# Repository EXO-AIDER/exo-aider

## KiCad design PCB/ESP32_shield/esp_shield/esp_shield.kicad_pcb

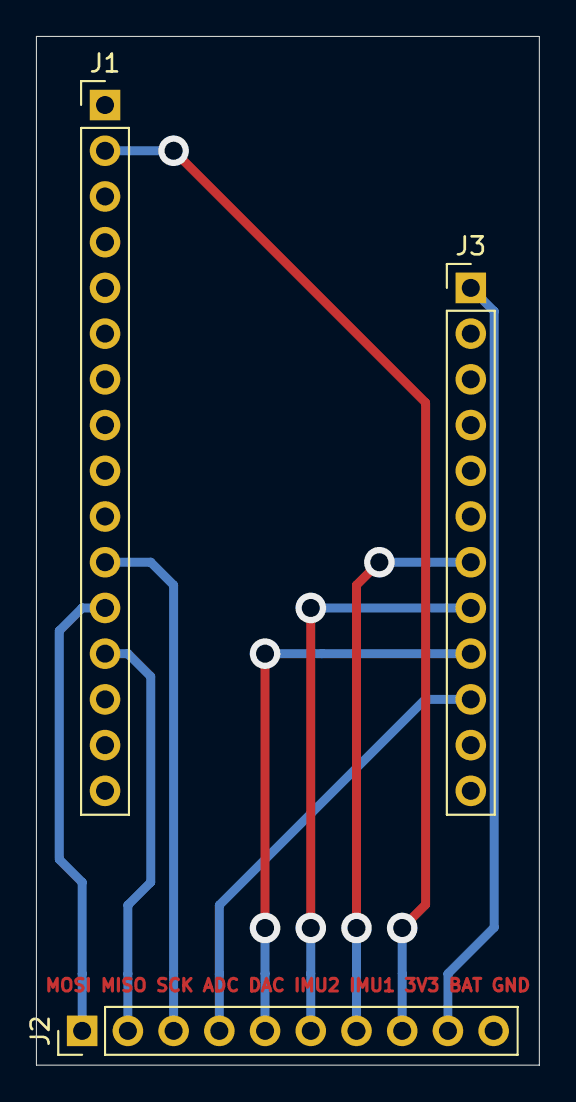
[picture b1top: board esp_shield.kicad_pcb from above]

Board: 2 copper layers, 27.9 x 57.2 mm, 3 parts (0 on the bottom side), 10 nets.

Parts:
J1: Conn_01x16; PinHeader_1x16_P2.54mm_Vertical
J2: Conn_01x10; PinHeader_1x10_P2.54mm_Vertical
J3: Conn_01x12; PinHeader_1x12_P2.54mm_Vertical

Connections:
3.3V: J1.2, J2.8
BAT: J2.9, J3.1
CS_ADC: J2.4, J3.10
CS_DAC: J2.5, J3.9
CS_IMU1: J2.7, J3.7
CS_IMU2: J2.6, J3.8
GND: J1.4, J2.10
MISO: J1.13, J2.2
MOSI: J1.12, J2.1
SCK: J1.11, J2.3

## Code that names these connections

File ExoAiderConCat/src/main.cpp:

#include <Arduino.h>
#include "BluetoothSerial.h" 
#include "TaskBT2.h"

#define CS_IMU1 15
#define CS_IMU2 33
#define CS_DAC 32
#define CS_ADC 14

BluetoothSerial ESP_BT; //Object for Bluetooth
TaskBT2 Task(CS_IMU1, CS_IMU2, CS_DAC, CS_ADC);   // pins for IMUs
std::vector<uint8_t> DataBufferBT;

// unsigned long dummy1, dummy2; // for timing - made by Simon

float SetVoltage = 0;

void setup() { 

  pinMode (LED_BUILTIN, OUTPUT); //Specify LED pin as output

  Serial.begin(115200); //Start Serial monitor in 9600
  Serial.println("");

  Task.BeginIMU();     // Initiate IMU
  Task.BeginDAC();     // Initiate DAC - Default output is set to zero volt
  Task.BeginADC();     // Initiate ADC
  
  /* Example: set DAC voltage channel [0 - 7] - input: [Channel, Voltage] 
     Erase this if not used! */
  Task.SetDACVoltaget(0, SetVoltage); 
  Task.SetDACVoltaget(1, SetVoltage); 
  Task.SetDACVoltaget(2, SetVoltage);
  Task.SetDACVoltaget(3, SetVoltage);
  Task.SetDACVoltaget(4, SetVoltage);
  Task.SetDACVoltaget(5, SetVoltage);
  Task.SetDACVoltaget(6, SetVoltage);
  Task.SetDACVoltaget(7, SetVoltage);
  // Example: Set DAC voltage end 

  // Bluetooth 
  ESP_BT.begin("Exo-Aider ESP32");                                    //Name of Bluetooth Device
  Serial.println("Bluetooth Device is Ready to Pair");
  while(ESP_BT.hasClient() == false){digitalWrite(LED_BUILTIN, LOW);} // Wait until a connection is established
  
  Serial.println("Device Connected"); 
  // Task.TestTask(); // Debugging erase this for
  
}


void loop() {  
  // auto start = micros();

  while(ESP_BT.hasClient() == false){digitalWrite(LED_BUILTIN, LOW);} // Check for client, if non, wait 
  digitalWrite(LED_BUILTIN, HIGH);

  if (ESP_BT.available())                                   // Check for received task over Bluetooth   
  {
    Task.SetTask(ESP_BT.read());                            // Check task to execute
  }
  
  if (Task.RunTask()){                                      // Check if task exsists         
    Task.ExecuteTask();                                     // Execute task 
    DataBufferBT = Task.GetSensorDataBT();                  // Get task/sensor data
    ESP_BT.write(DataBufferBT.data(), DataBufferBT.size()); // Send data over Bluetooth
    
  }

  // cout << "Sample frequency: " << 1/((micros() - start)*1e-6) << " Hz" << endl;

}

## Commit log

2020-01-09 Added all files from Simon and the files i have made myself
2020-01-09 ESP2Matlab folder added
2020-01-10 added matlab script for testing different notch filters
2020-01-13 50 Hz notch filter implemented in matlab. Pinout for sEMG board is made
2020-01-14 data from filter analysis including a wip matlab script for visualization
2020-01-17 timing added to C++ program and some data and analysis from emg signals are added to MAtlab scripts
2020-01-20 Changed names in matlab matrix to fit FSR pins on PCB. Pins has to be moved on next PCB iteration. Added more datafiles from filter and diff amp measurements
2020-01-21 Removed submodules
2020-01-21 Added missing folder, timing need to be rewritten
2020-01-21 Everything should be fine again now
2020-01-21 Sample frequency in main loop
2020-01-22 Sending and receiving gyro data
2020-01-23 included gyro data in "all" function and simplified timer
2020-01-30 Sped up SPI clock to get a more reliable sample frequency
2020-02-04 Added plots for all signals after measuring incl. FFT
2020-02-05 Trying to make FSR 5 and 6 work. Still not working
2020-02-10 changed some clk freqs with great results. Everything is working
    two FSR sensors has an offset but is fixed by swapping resistors on DAC feedback
2020-02-14 Small changes
2020-02-27 added python venv
2020-03-23 armband update document
2020-03-26 new bluetooth from Simon
2020-03-27 new bluetooth, should work, need hardware
2020-03-31 new bluetooth with all datacollection implemented. Need to be tested with hardware
2020-04-30 matlab for bluetooth. All sensors added
2020-05-12 added real time plotting to matlab
2020-07-20 Small changed, nothing special + schematics
2020-07-28 pcb for esp32 and minor software changes
2020-07-31 Code works now. moved class initialization global
2020-11-05 dunno
